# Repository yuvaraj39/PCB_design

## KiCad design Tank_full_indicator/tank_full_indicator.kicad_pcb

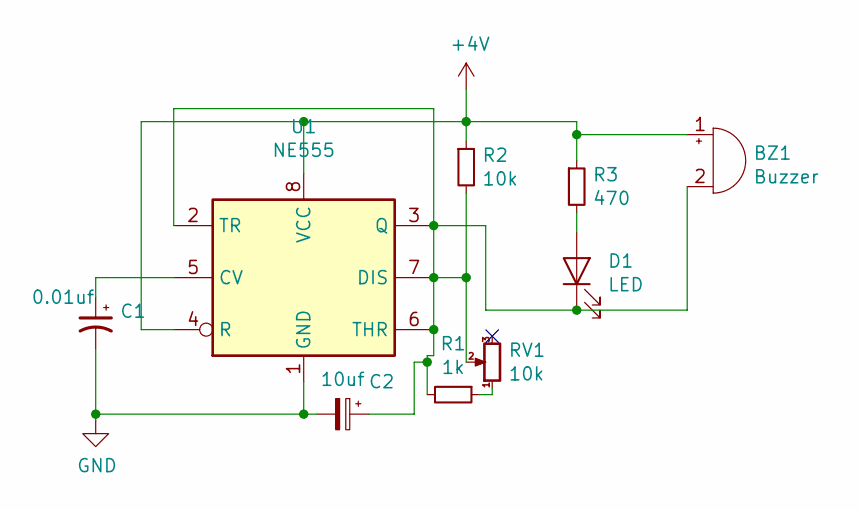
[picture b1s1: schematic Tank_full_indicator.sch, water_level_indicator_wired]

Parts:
BZ1: Buzzer; Buzzer_12x9.5RM7.6
C1: 0.01uf; CP_Radial_Tantal_D6.0mm_P2.50mm
C2: 10uf; CP_Radial_Tantal_D6.0mm_P5.00mm
D1: LED; LED_D3.0mm
R1: 1k; R_Axial_DIN0411_L9.9mm_D3.6mm_P15.24mm_Horizontal
R2: 10k; R_Axial_DIN0411_L9.9mm_D3.6mm_P15.24mm_Horizontal
R3: 470; R_Axial_DIN0411_L9.9mm_D3.6mm_P15.24mm_Horizontal
RV1: 10k; Potentiometer_Bourns_3339P_Vertical_HandSoldering
U1: NE555; DIP-8_W7.62mm

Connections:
+4V: BZ1.1 (-), R2.1, R3.1, U1.4 (R), U1.8 (VCC)
GND: C1.2, C2.2, U1.1 (GND)
unnamed: BZ1.2 (+), C2.1, D1.1 (K), R1.2, R2.2, RV1.2, U1.2 (TR), U1.3 (Q), U1.6 (THR), U1.7 (DIS)
unnamed: C1.1, U1.5 (CV)
unnamed: D1.2 (A), R3.2
unnamed: R1.1, RV1.1

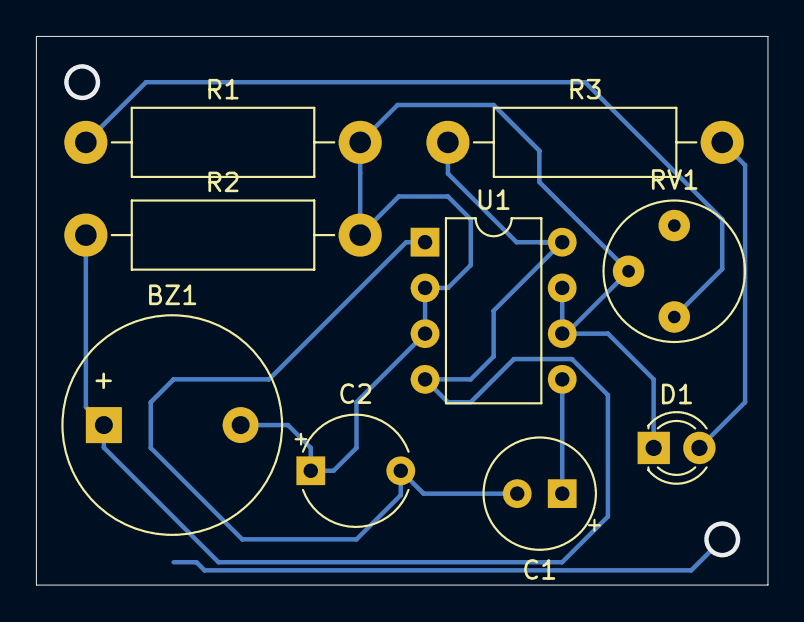
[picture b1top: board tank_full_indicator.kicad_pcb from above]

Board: 2 copper layers, 40.6 x 30.5 mm, 9 parts (0 on the bottom side), 6 nets.
